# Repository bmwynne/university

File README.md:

# university
* Repo containing various projects from Indiana University courses.
* IOS Dev
* Embedded Systems Dev
* Algorithm in Python
* Software Defined Networks and HDL simulation
* Verilog and FPGA Development
* Operating System Development
* Particle Physics Simulation
* Eagle Cad Schematics

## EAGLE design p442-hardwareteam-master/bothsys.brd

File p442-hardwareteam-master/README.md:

p442-hardwareteam
=================

DNR Project - The Hardware Team

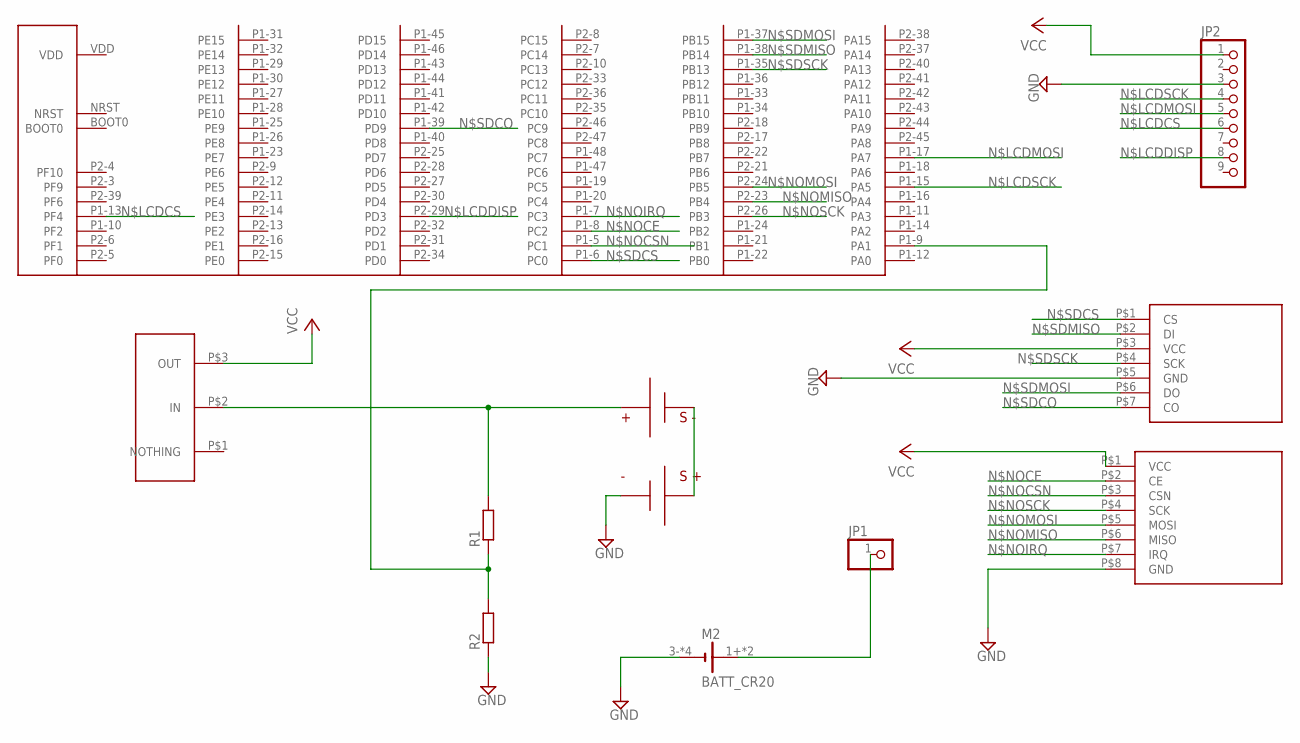
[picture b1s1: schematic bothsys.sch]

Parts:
JP1: PINHD-1X1; 1X01
JP2: PINHD-1X9; 1X09
M2: BATT_CR20
R1, R2: R-EU_R0805; R0805
ST1: STM32_F3; STM32F3
U$1: SDCARD
U$2: NORDIC_NRF24L01
U$3: OS102011MA1QN1
U$4: OURBATT

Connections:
5V: ST1.5V-A (5V), ST1.5V-B (5V)
GND: JP2.3, M2.3- (-), M2.4- (-), M2.5- (-), M2.6- (-), R2.1, ST1.GND1 (GND), ST1.GND2 (GND), ST1.GND3 (GND), ST1.GND4 (GND), ST1.GND5 (GND), ST1.GND6 (GND), ST1.GND7 (GND), ST1.GND8 (GND), ST1.GND9 (GND), U$1.P$5 (GND), U$2.P$8 (GND), U$4.- (GROUND)
unnamed: JP1.1, M2.1+ (+), M2.2+ (+)
unnamed: R1.2, U$3.P$2 (IN), U$4.+ (POWER)
unnamed: U$4.SERIESNEG, U$4.SERIESPOS
unnamed: R1.1, R2.2, ST1.P1-9 (PA1)
N$LCDCS: JP2.6, ST1.P1-13 (PF4)
N$LCDDISP: JP2.8, ST1.P2-29 (PD3)
N$LCDMOSI: JP2.5, ST1.P1-17 (PA7)
N$LCDSCK: JP2.4, ST1.P1-15 (PA5)
N$NOCE: ST1.P1-8 (PC2), U$2.P$2 (CE)
N$NOCSN: ST1.P1-5 (PC1), U$2.P$3 (CSN)
N$NOIRQ: ST1.P1-7 (PC3), U$2.P$7 (IRQ)
N$NOMISO: ST1.P2-23 (PB4), U$2.P$6 (MISO)
N$NOMOSI: ST1.P2-24 (PB5), U$2.P$5 (MOSI)
N$NOSCK: ST1.P2-26 (PB3), U$2.P$4 (SCK)
N$SDCO: ST1.P1-39 (PD9), U$1.P$7 (CO)
N$SDCS: ST1.P1-6 (PC0), U$1.P$1 (CS)
N$SDMISO: ST1.P1-38 (PB14), U$1.P$2 (DI)
N$SDMOSI: ST1.P1-37 (PB15), U$1.P$6 (DO)
N$SDSCK: ST1.P1-35 (PB13), U$1.P$4 (SCK)
VCC: JP2.1, ST1.3V-A (VCC), ST1.3V-B (VCC), U$1.P$3 (VCC), U$2.P$1 (VCC), U$3.P$3 (OUT)
VDD: ST1.VDD

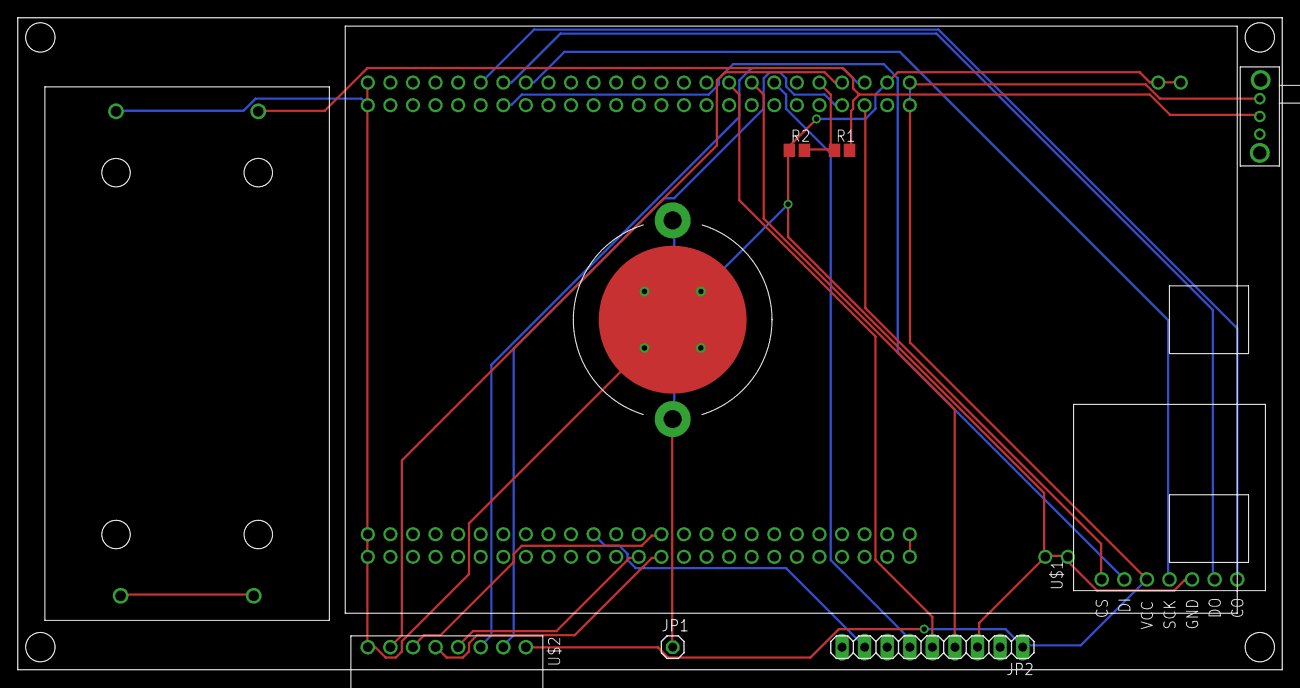
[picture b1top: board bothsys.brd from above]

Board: 2 copper layers, 142.2 x 73.3 mm, 10 parts (0 on the bottom side), 22 nets.

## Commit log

2017-11-15 pushing all files to github for storage.. rip enterprise github
